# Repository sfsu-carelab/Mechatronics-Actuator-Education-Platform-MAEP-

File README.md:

# Mechatronics-Actuator-Education-Platform-MAEP-
The proposed laboratory curriculum encompasses an all-in-one mechatronics actuator test platform for the study of fundamental actuator technologies, 
including a direct current brushed motor, stepper, and radio control servo motor that is generally taught in an undergraduate mechatronics course.  

The available files include the design CAD part files and PCB Eagle ciruit schematics to recreate the actuator test plaform as a teaching laboratory equipment.  Datasheets and documentation of the motors used are available including pictures of the final built platform.  Design adjustments would need to be made if mounting motors from different vendor and model number.

An example lab manual with sample code is provided for operating the brushed dc motor for learners to develop their own motor drive modes using an H-Bridge driver.

This work is referenced below and please cite our work if you use our education platform design for your curriculum.
Hulse, O., Verma, K., Diaz, K., Jung, H. S., and Quintero, D., “Work-in-Progress: All-In-One, Open Source Mechatronics Actuator Education Platform for Active Learning Curriculum,” in ASEE Annual Conference, Portland, Oregon, 2024.

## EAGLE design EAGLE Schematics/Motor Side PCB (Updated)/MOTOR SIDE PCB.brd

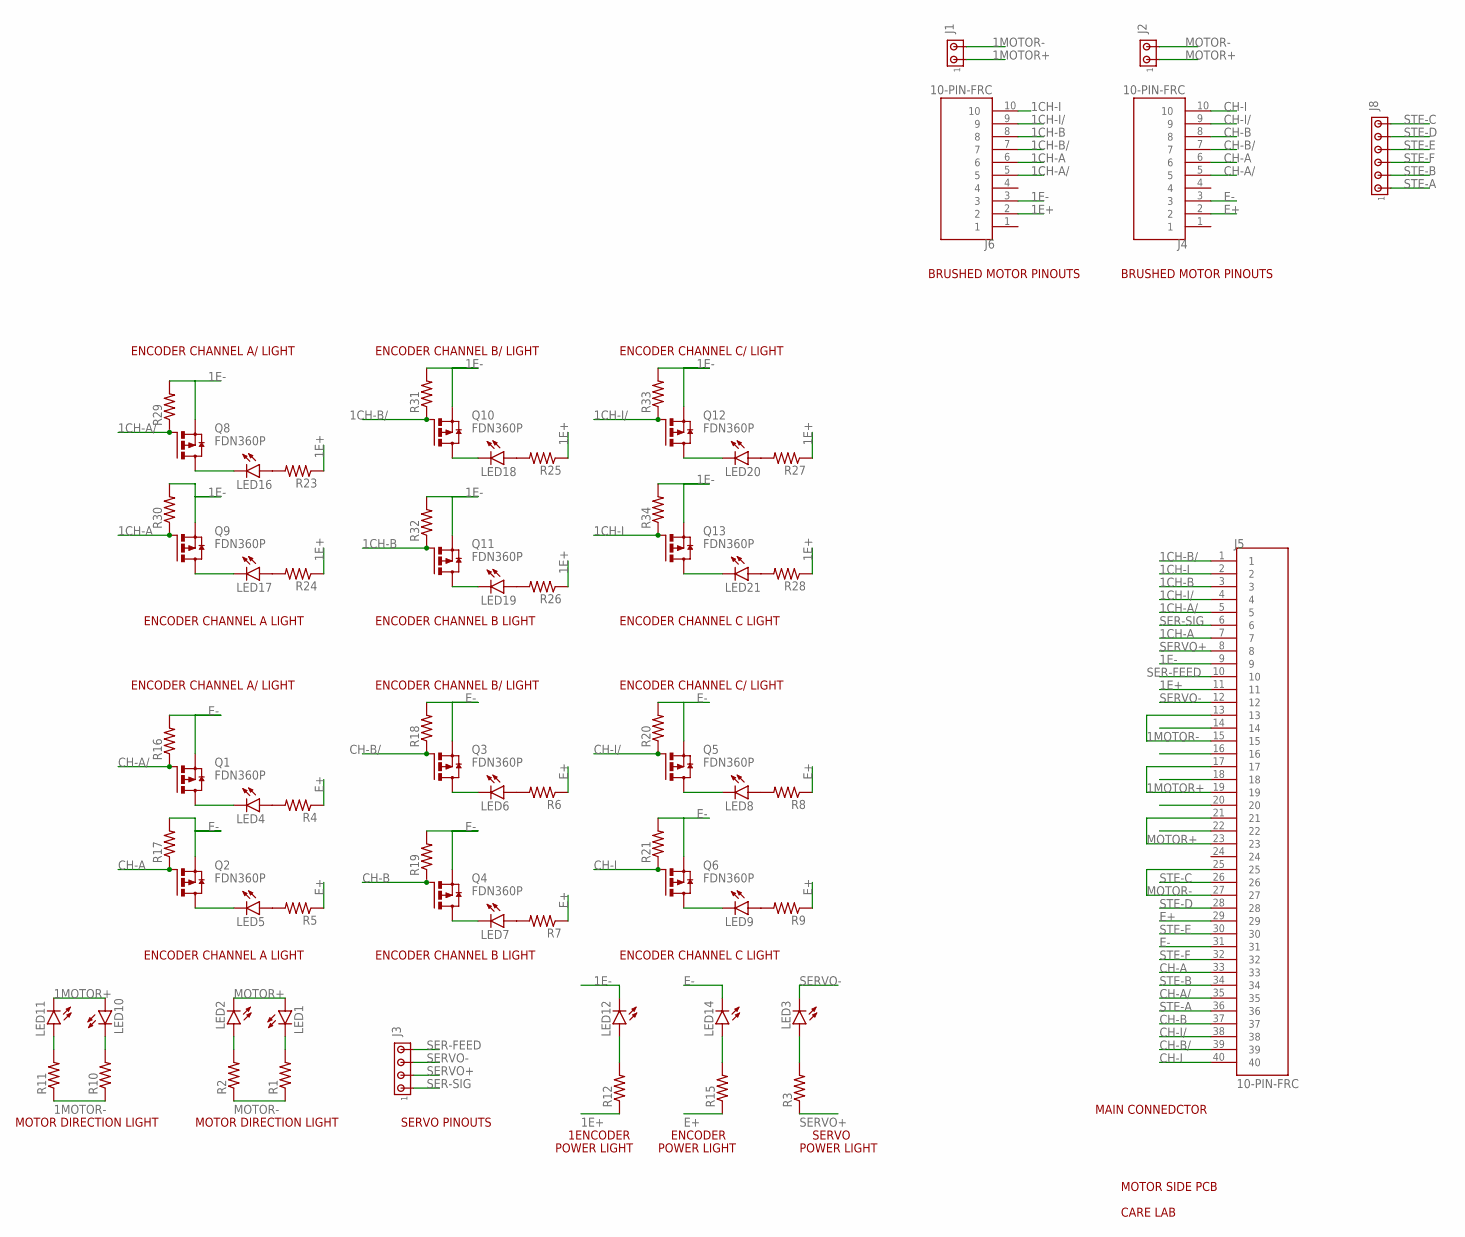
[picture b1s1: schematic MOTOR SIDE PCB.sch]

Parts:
J1, J2: MTA02-100; 10X02MTA
J3: MTA04-100; 10X04MTA
J4, J6: 10-PIN-FRC; TE_2-1761603-3
J5: 10-PIN-FRC; TE_3-1761605-3
J8: MTA06-100; 10X06MTA
LED1, LED2, LED3, LED4, LED5, LED6, LED7, LED8, LED9, LED10, LED11, LED12, LED14, LED16, LED17, LED18, LED19, LED20, LED21: LEDCHIP-LED0805; CHIP-LED0805
Q1, Q2, Q3, Q4, Q5, Q6, Q8, Q9, Q10, Q11, Q12, Q13: FDN360P; SUPER-SOT3
R1, R2, R3, R4, R5, R6, R7, R8, R9, R10, R11, R12, R15, R16, R17, R18, R19, R20, R21, R23, R24, R25, R26, R27, R28, R29, R30, R31, R32, R33, R34: R-US_R0603; R0603

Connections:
1CH-A: J5.7, J6.6, Q9.1 (G), R30.1
1CH-A/: J5.5, J6.5, Q8.1 (G), R29.1
1CH-B: J5.3, J6.8, Q11.1 (G), R32.1
1CH-B/: J5.1, J6.7, Q10.1 (G), R31.1
1CH-I: J5.2, J6.10, Q13.1 (G), R34.1
1CH-I/: J5.4, J6.9, Q12.1 (G), R33.1
1E+: J5.11, J6.2, R12.1, R23.1, R24.1, R25.1, R26.1, R27.1, R28.1
1E-: J5.9, J6.3, LED12.C, Q8.2 (S), Q9.2 (S), Q10.2 (S), Q11.2 (S), Q12.2 (S), Q13.2 (S), R29.2, R30.2, R31.2, R32.2, R33.2, R34.2
1MOTOR+: J1.1, J5.17, J5.19, LED10.A, LED11.C
1MOTOR-: J1.2, J5.13, J5.15, R10.1, R11.1
CH-A: J4.6, J5.33, Q2.1 (G), R17.1
CH-A/: J4.5, J5.35, Q1.1 (G), R16.1
CH-B: J4.8, J5.37, Q4.1 (G), R19.1
CH-B/: J4.7, J5.39, Q3.1 (G), R18.1
CH-I: J4.10, J5.40, Q6.1 (G), R21.1
CH-I/: J4.9, J5.38, Q5.1 (G), R20.1
E+: J4.2, J5.29, R4.1, R5.1, R6.1, R7.1, R8.1, R9.1, R15.1
E-: J4.3, J5.31, LED14.C, Q1.2 (S), Q2.2 (S), Q3.2 (S), Q4.2 (S), Q5.2 (S), Q6.2 (S), R16.2, R17.2, R18.2, R19.2, R20.2, R21.2
MOTOR+: J2.1, J5.21, J5.23, LED1.A, LED2.C
MOTOR-: J2.2, J5.25, J5.27, R1.1, R2.1
unnamed: LED4.A, R4.2
unnamed: LED5.A, R5.2
unnamed: LED6.A, R6.2
unnamed: LED7.A, R7.2
unnamed: LED8.A, R8.2
unnamed: LED9.A, R9.2
unnamed: LED2.A, R2.2
unnamed: LED1.C, R1.2
unnamed: LED11.A, R11.2
unnamed: LED10.C, R10.2
unnamed: LED12.A, R12.2
unnamed: LED4.C, Q1.3 (D)
unnamed: LED5.C, Q2.3 (D)
unnamed: LED6.C, Q3.3 (D)
unnamed: LED7.C, Q4.3 (D)
unnamed: LED8.C, Q5.3 (D)
unnamed: LED9.C, Q6.3 (D)
unnamed: LED16.C, Q8.3 (D)
unnamed: LED17.C, Q9.3 (D)
unnamed: LED18.C, Q10.3 (D)
unnamed: LED19.C, Q11.3 (D)
unnamed: LED20.C, Q12.3 (D)
unnamed: LED3.A, R3.2
unnamed: LED14.A, R15.2
unnamed: LED21.C, Q13.3 (D)
unnamed: LED16.A, R23.2
unnamed: LED17.A, R24.2
unnamed: LED18.A, R25.2
unnamed: LED19.A, R26.2
unnamed: LED20.A, R27.2
unnamed: LED21.A, R28.2
SER-FEED: J3.4, J5.10
SER-SIG: J3.1, J5.6
SERVO+: J3.2, J5.8, R3.1
SERVO-: J3.3, J5.12, LED3.C
STE-A: J5.36, J8.1
STE-B: J5.34, J8.2
STE-C: J5.26, J8.6
STE-D: J5.28, J8.5
STE-E: J5.30, J8.4
STE-F: J5.32, J8.3

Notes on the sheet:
ENCODER CHANNEL A LIGHT
ENCODER CHANNEL B LIGHT
ENCODER CHANNEL C LIGHT
ENCODER CHANNEL C/ LIGHT
ENCODER CHANNEL B/ LIGHT
ENCODER CHANNEL A/ LIGHT
MOTOR DIRECTION LIGHT
ENCODER
POWER LIGHT
SERVO
SERVO PINOUTS
BRUSHED MOTOR PINOUTS
MAIN CONNEDCTOR
MOTOR SIDE PCB
CARE LAB
1ENCODER

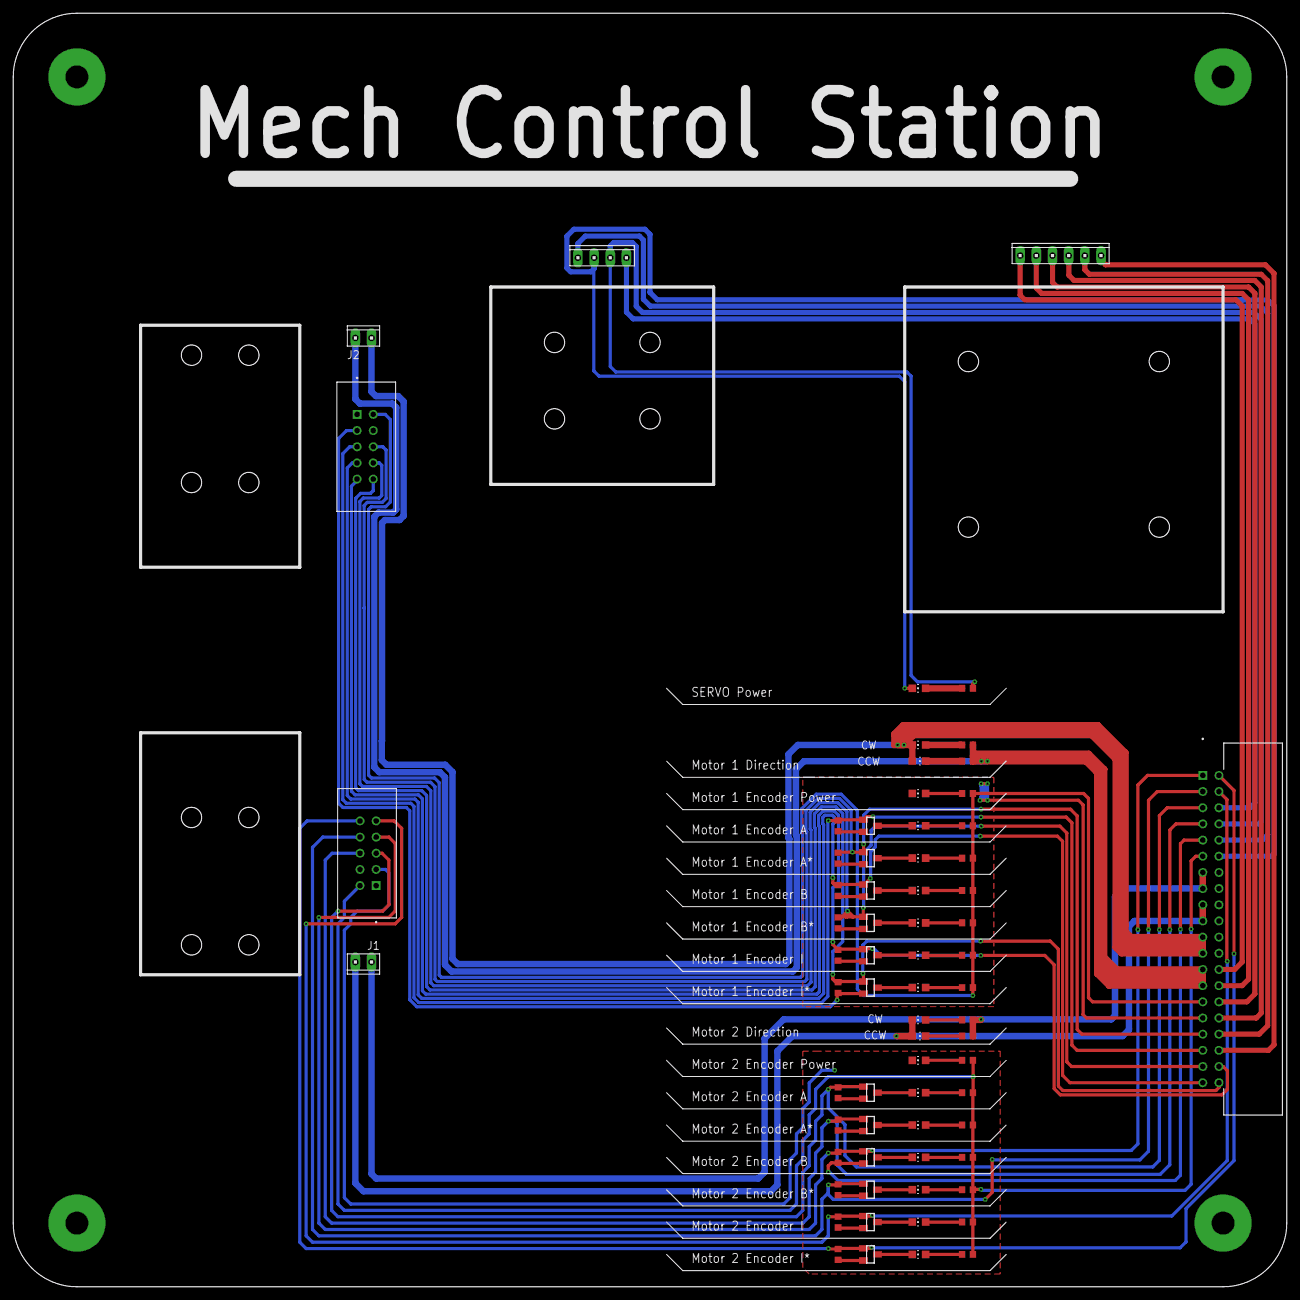
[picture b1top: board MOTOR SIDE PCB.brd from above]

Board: 2 copper layers, 200.0 x 200.0 mm, 69 parts (0 on the bottom side), 61 nets.

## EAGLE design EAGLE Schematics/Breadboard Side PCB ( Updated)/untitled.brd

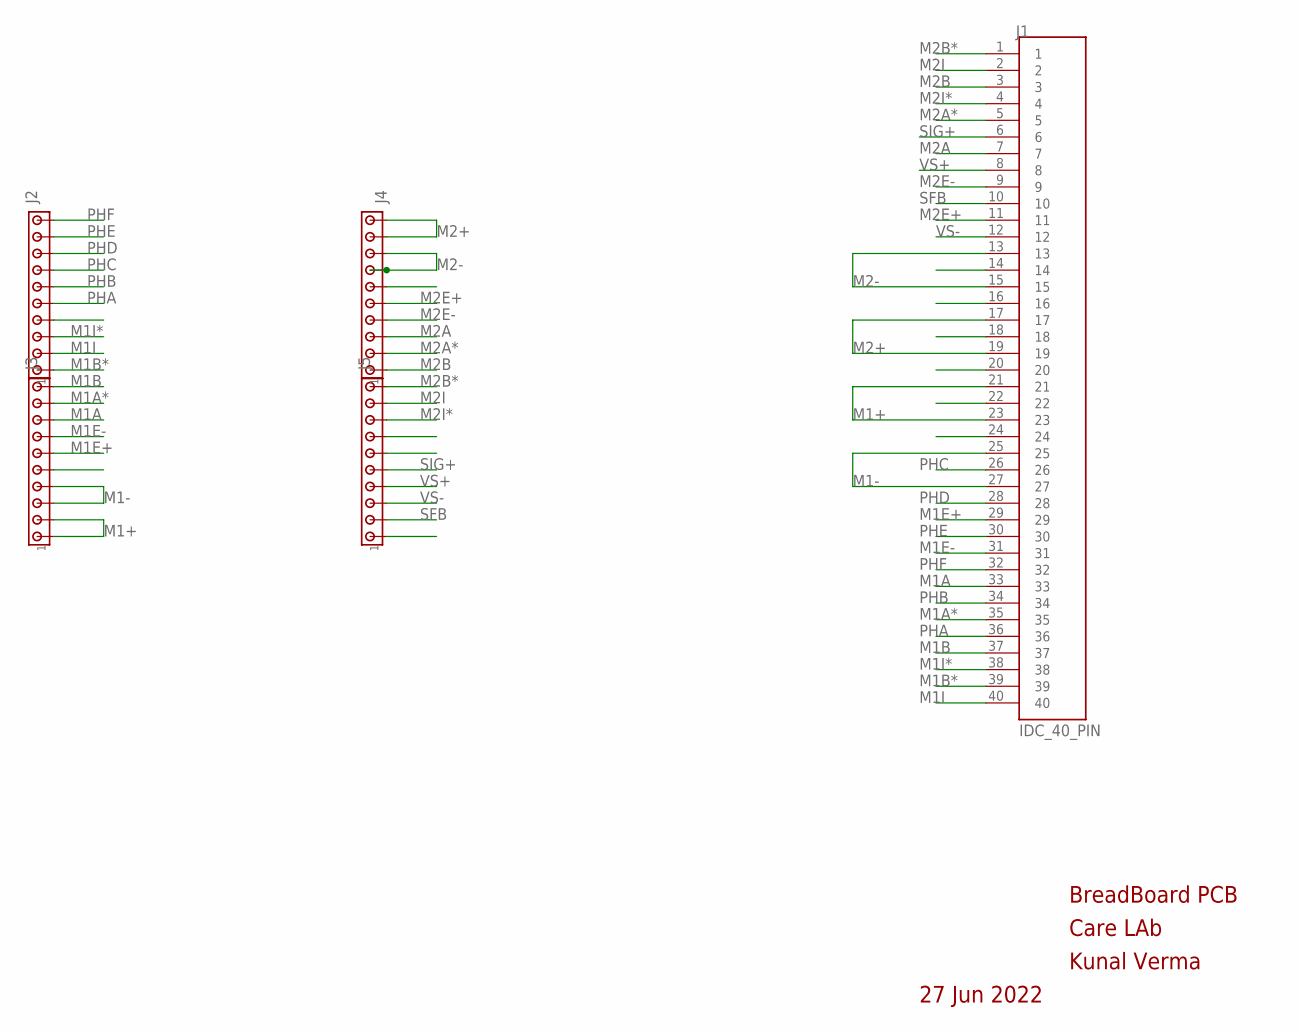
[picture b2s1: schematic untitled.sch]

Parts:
J1: IDC_40_PIN; TE_3-1761605-3
J2, J3, J4, J5: MTA10-100; 10X10MTA

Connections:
M1+: J1.21, J1.23, J3.1, J3.2
M1-: J1.25, J1.27, J3.3, J3.4
M1A: J1.33, J3.8
M1A*: J1.35, J3.9
M1B: J1.37, J3.10
M1B*: J1.39, J2.1
M1E+: J1.29, J3.6
M1E-: J1.31, J3.7
M1I: J1.40, J2.2
M1I*: J1.38, J2.3
M2+: J1.17, J1.19, J4.9, J4.10
M2-: J1.13, J1.15, J4.7, J4.8
M2A: J1.7, J4.3
M2A*: J1.5, J4.2
M2B: J1.3, J4.1
M2B*: J1.1, J5.10
M2E+: J1.11, J4.5
M2E-: J1.9, J4.4
M2I: J1.2, J5.9
M2I*: J1.4, J5.8
PHA: J1.36, J2.5
PHB: J1.34, J2.6
PHC: J1.26, J2.7
PHD: J1.28, J2.8
PHE: J1.30, J2.9
PHF: J1.32, J2.10
SFB: J1.10, J5.2
SIG+: J1.6, J5.5
VS+: J1.8, J5.4
VS-: J1.12, J5.3

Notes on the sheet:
BreadBoard PCB
Care LAb
Kunal Verma
27 Jun 2022

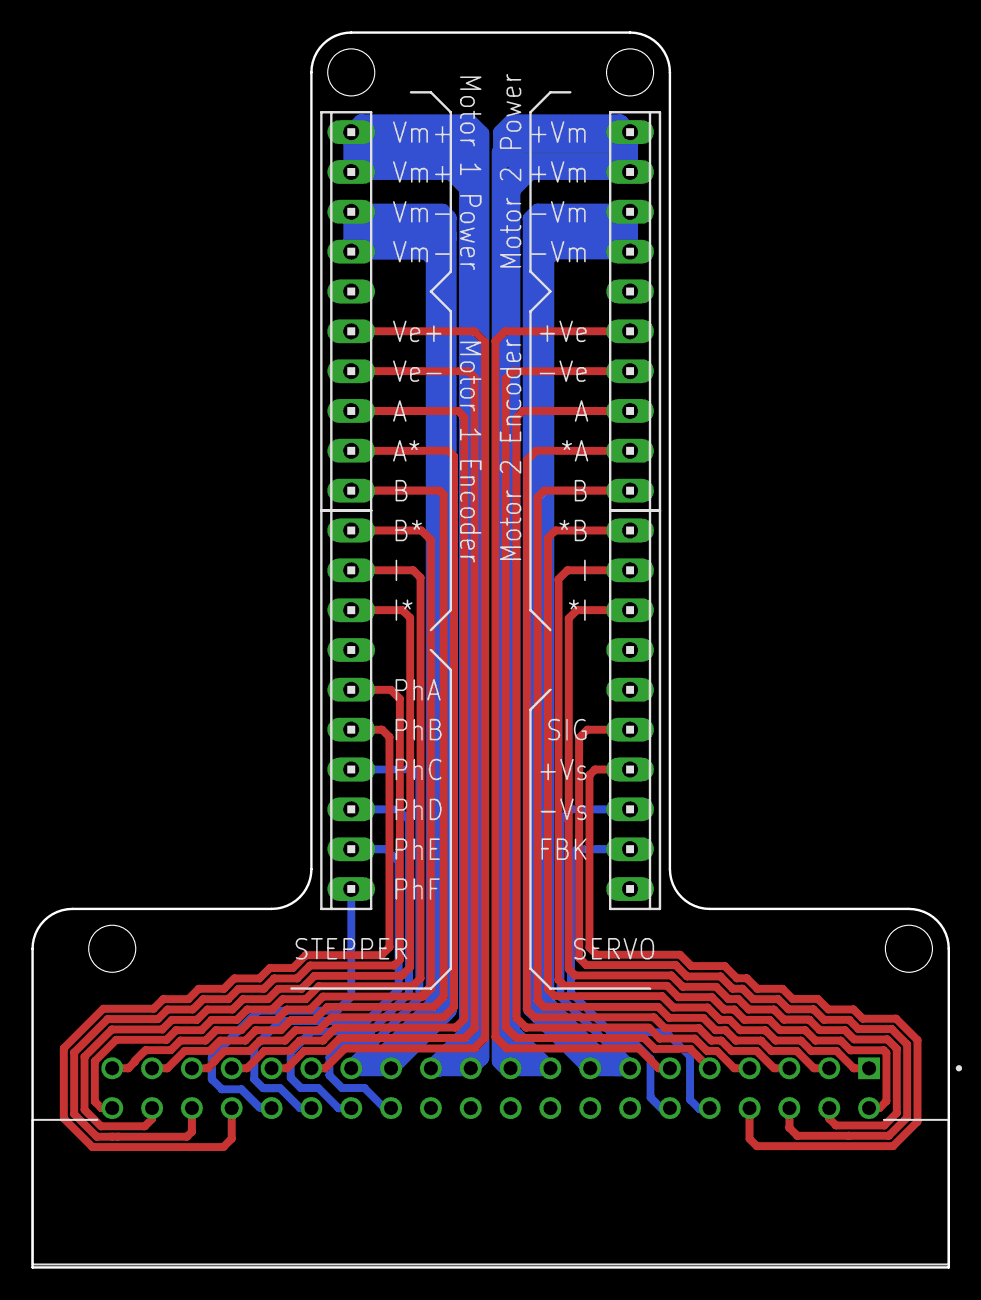
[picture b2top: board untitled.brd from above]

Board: 2 copper layers, 58.4 x 78.7 mm, 5 parts (0 on the bottom side), 30 nets.

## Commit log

2024-04-30 Create Datasheets
2024-04-30 Create Lab Manual
